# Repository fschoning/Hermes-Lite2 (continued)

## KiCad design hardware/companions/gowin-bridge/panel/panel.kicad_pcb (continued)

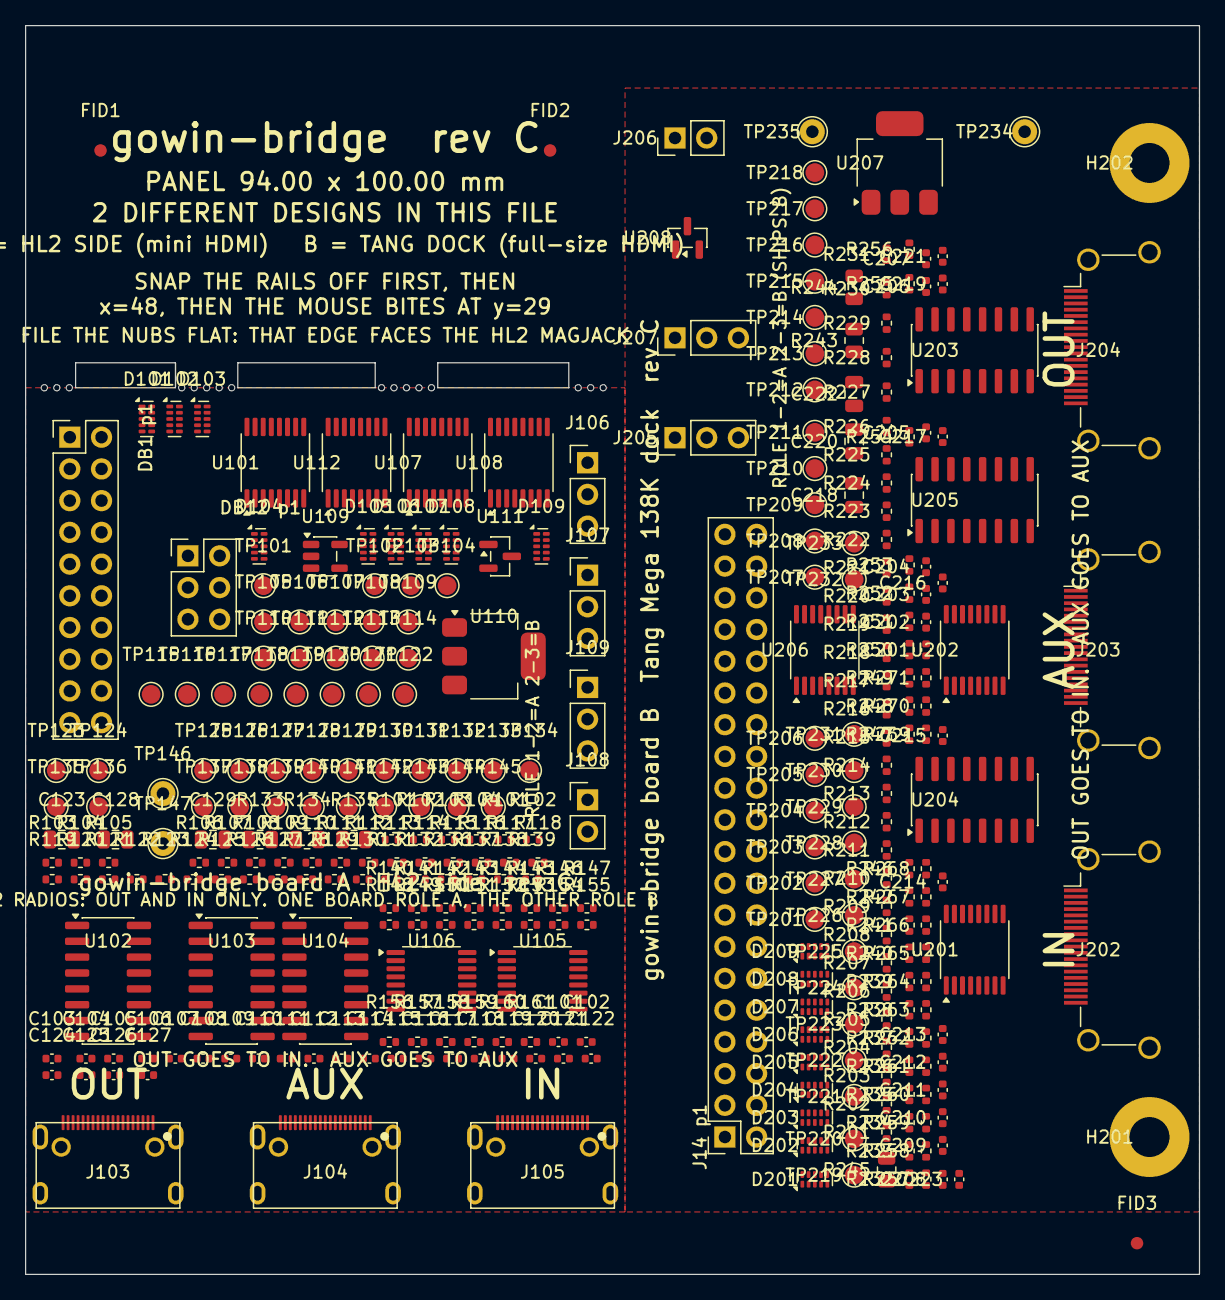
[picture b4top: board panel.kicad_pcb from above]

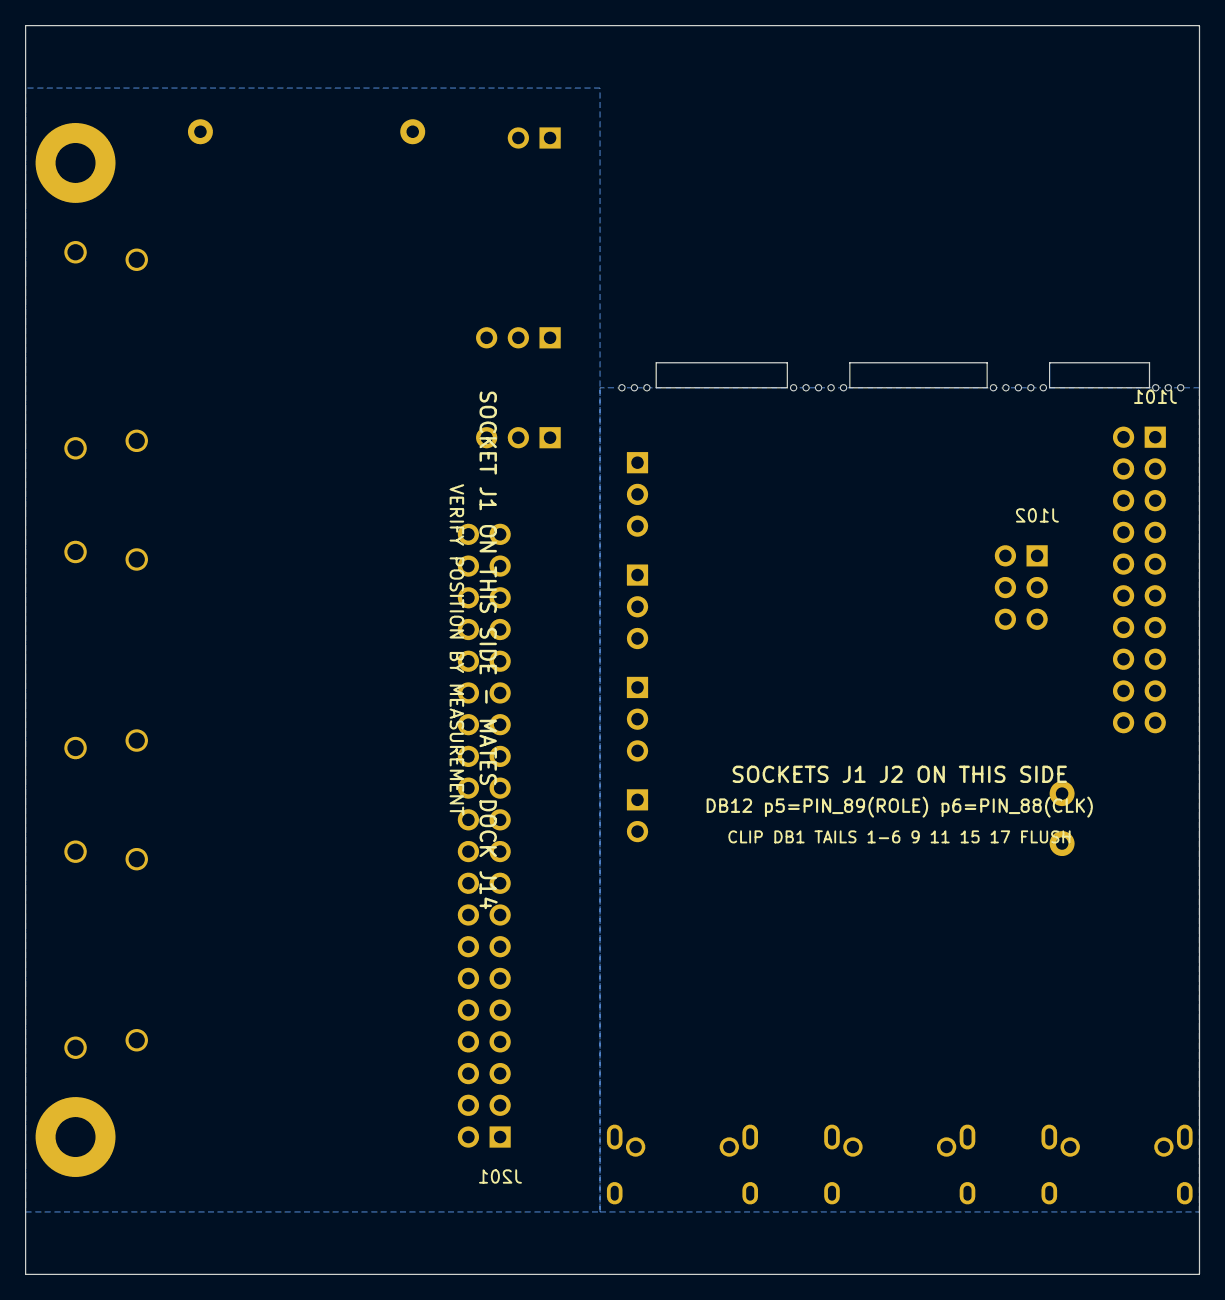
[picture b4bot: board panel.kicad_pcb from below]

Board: 4 copper layers, 94.0 x 100.0 mm, 345 parts (3 on the bottom side), 180 nets, no tracks yet.

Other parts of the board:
MB1, MB2, MB3, MB4, MB5, MB6, MB7, MB8, MB9, MB10, MB11, MB12, MB13, MB14, MB15, MB16: Drill
R101#2, R102#2, R103#2, R104#2: 10k; R_0402_1005Metric

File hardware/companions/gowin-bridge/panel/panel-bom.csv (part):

Designator,Value,Footprint,LCSC,MfrPart,Populate,Function,Note
C101,100nF,C_0402_1005Metric,C1525,,DNP,"AC-coupling option, I CLK P leg",NOT FITTED. Fit only together with the VBIAS network and remove the parallel 0 R link. Needs DC-balanced data; the gateware does not guarantee that.
C102,100nF,C_0402_1005Metric,C1525,,DNP,"AC-coupling option, I CLK N leg",NOT FITTED. Fit only together with the VBIAS network and remove the parallel 0 R link. Needs DC-balanced data; the gateware does not guarantee that.
C103,100nF,C_0402_1005Metric,C1525,,DNP,"AC-coupling option, I D0 P leg",NOT FITTED. Fit only together with the VBIAS network and remove the parallel 0 R link. Needs DC-balanced data; the gateware does not guarantee that.
C104,100nF,C_0402_1005Metric,C1525,,DNP,"AC-coupling option, I D0 N leg",NOT FITTED. Fit only together with the VBIAS network and remove the parallel 0 R link. Needs DC-balanced data; the gateware does not guarantee that.
C105,100nF,C_0402_1005Metric,C1525,,DNP,"AC-coupling option, I D1 P leg",NOT FITTED. Fit only together with the VBIAS network and remove the parallel 0 R link. Needs DC-balanced data; the gateware does not guarantee that.
C106,100nF,C_0402_1005Metric,C1525,,DNP,"AC-coupling option, I D1 N leg",NOT FITTED. Fit only together with the VBIAS network and remove the parallel 0 R link. Needs DC-balanced data; the gateware does not guarantee that.
C107,100nF,C_0402_1005Metric,C1525,,DNP,"AC-coupling option, I D2 P leg",NOT FITTED. Fit only together with the VBIAS network and remove the parallel 0 R link. Needs DC-balanced data; the gateware does not guarantee that.
C108,100nF,C_0402_1005Metric,C1525,,DNP,"AC-coupling option, I D2 N leg",NOT FITTED. Fit only together with the VBIAS network and remove the parallel 0 R link. Needs DC-balanced data; the gateware does not guarantee that.
C109,100nF,C_0402_1005Metric,C1525,,DNP,VBIAS bypass,NOT FITTED. Part of the AC-coupling option.
C110,100nF,C_0402_1005Metric,C1525,,yes,U1 VCCB,
C111,100nF,C_0402_1005Metric,C1525,,yes,U1 VCCA,
C112,100nF,C_0402_1005Metric,C1525,,yes,U12 VCCB,
C113,100nF,C_0402_1005Metric,C1525,,yes,U12 VCCA,
C114,100nF,C_0402_1005Metric,C1525,,yes,U2 VCC,
C115,100nF,C_0402_1005Metric,C1525,,yes,U3 VCC,
C116,100nF,C_0402_1005Metric,C1525,,yes,U4 VCC,
C117,100nF,C_0402_1005Metric,C1525,,yes,U5 VCC,
C118,100nF,C_0402_1005Metric,C1525,,yes,U6 VCC,
C119,100nF,C_0402_1005Metric,C1525,,yes,U7 VCCA,
C120,100nF,C_0402_1005Metric,C1525,,yes,U7 VCCB,
C121,100nF,C_0402_1005Metric,C1525,,yes,U8 VCCA,
C122,100nF,C_0402_1005Metric,C1525,,yes,U8 VCCB,
C123,10uF,C_0805_2012Metric,C15850,,yes,+3V3 bulk,
C124,100nF,C_0402_1005Metric,C1525,,yes,+3V3 bulk HF,
C125,1uF,C_0402_1005Metric,C52923,,yes,U9 output,
C126,100nF,C_0402_1005Metric,C1525,,yes,U9 input,
C127,100nF,C_0402_1005Metric,C1525,,yes,DB1 +3V3 entry,
C128,10uF,C_0805_2012Metric,C15850,,yes,U10 input bulk (option),
C129,10uF,C_0805_2012Metric,C15850,,yes,U10 output bulk (option),
C201,22pF,C_0402_1005Metric,C1555,,DNP,Optional ringing damper on LINK_SLOW_IN,NOT FITTED. 22 pF into 100 R is 2.2 ns. Fit if the unterminated cable wire rings enough to double-clock the receiver.
C202,100nF,C_0402_1005Metric,C1525,,DNP,"AC-coupling option, I CLK P leg",NOT FITTED. Fit only together with the VBIAS network and remove the parallel 0 R link. Needs DC-balanced data; the gateware does not guarantee that.
C203,100nF,C_0402_1005Metric,C1525,,DNP,"AC-coupling option, I CLK N leg",NOT FITTED. Fit only together with the VBIAS network and remove the parallel 0 R link. Needs DC-balanced data; the gateware does not guarantee that.
C204,100nF,C_0402_1005Metric,C1525,,DNP,"AC-coupling option, I D0 P leg",NOT FITTED. Fit only together with the VBIAS network and remove the parallel 0 R link. Needs DC-balanced data; the gateware does not guarantee that.
C205,100nF,C_0402_1005Metric,C1525,,DNP,"AC-coupling option, I D0 N leg",NOT FITTED. Fit only together with the VBIAS network and remove the parallel 0 R link. Needs DC-balanced data; the gateware does not guarantee that.
C206,100nF,C_0402_1005Metric,C1525,,DNP,"AC-coupling option, I D1 P leg",NOT FITTED. Fit only together with the VBIAS network and remove the parallel 0 R link. Needs DC-balanced data; the gateware does not guarantee that.
C207,100nF,C_0402_1005Metric,C1525,,DNP,"AC-coupling option, I D1 N leg",NOT FITTED. Fit only together with the VBIAS network and remove the parallel 0 R link. Needs DC-balanced data; the gateware does not guarantee that.
C208,100nF,C_0402_1005Metric,C1525,,DNP,"AC-coupling option, I D2 P leg",NOT FITTED. Fit only together with the VBIAS network and remove the parallel 0 R link. Needs DC-balanced data; the gateware does not guarantee that.
C209,100nF,C_0402_1005Metric,C1525,,DNP,"AC-coupling option, I D2 N leg",NOT FITTED. Fit only together with the VBIAS network and remove the parallel 0 R link. Needs DC-balanced data; the gateware does not guarantee that.
C210,100nF,C_0402_1005Metric,C1525,,DNP,VBIAS bypass,NOT FITTED. Part of the AC-coupling option.
C211,100nF,C_0402_1005Metric,C1525,,yes,U1 VCC,
C212,100nF,C_0402_1005Metric,C1525,,yes,U2 VCC,
C213,100nF,C_0402_1005Metric,C1525,,yes,U3 VCC,
C214,100nF,C_0402_1005Metric,C1525,,yes,U4 VCC,
C215,100nF,C_0402_1005Metric,C1525,,yes,U5 VCC,
C216,100nF,C_0402_1005Metric,C1525,,yes,U6 VCCA,
C217,100nF,C_0402_1005Metric,C1525,,yes,U6 VCCB,
C218,10uF,C_0805_2012Metric,C15850,,yes,+3V3 bulk,
C219,100nF,C_0402_1005Metric,C1525,,yes,+3V3 bulk HF,
C220,10uF,C_0805_2012Metric,C15850,,yes,5 V input bulk,
C221,100nF,C_0402_1005Metric,C1525,,yes,5 V input HF,
C222,10uF,C_0805_2012Metric,C15850,,yes,U7 output bulk,
C223,100nF,C_0402_1005Metric,C1525,,yes,extra +3V3,
D101,TPD4E05U06,USON-10_2.5x1.0mm_P0.5mm,C138714,TPD4E05U06DQAR,yes,"Quad 0.5 pF ESD array, 5.5 V, USON-10","Place within 5 mm of the HDMI connector pins, on the connector side of everything else."
D102,TPD4E05U06,USON-10_2.5x1.0mm_P0.5mm,C138714,TPD4E05U06DQAR,yes,"Quad 0.5 pF ESD array, 5.5 V, USON-10","Place within 5 mm of the HDMI connector pins, on the connector side of everything else."
D103,TPD4E05U06,USON-10_2.5x1.0mm_P0.5mm,C138714,TPD4E05U06DQAR,yes,"Quad 0.5 pF ESD array, 5.5 V, USON-10","Place within 5 mm of the HDMI connector pins, on the connector side of everything else."
D104,TPD4E05U06,USON-10_2.5x1.0mm_P0.5mm,C138714,TPD4E05U06DQAR,yes,"Quad 0.5 pF ESD array, 5.5 V, USON-10","Place within 5 mm of the HDMI connector pins, on the connector side of everything else."
D105,TPD4E05U06,USON-10_2.5x1.0mm_P0.5mm,C138714,TPD4E05U06DQAR,yes,"Quad 0.5 pF ESD array, 5.5 V, USON-10","Place within 5 mm of the HDMI connector pins, on the connector side of everything else."
D106,TPD4E05U06,USON-10_2.5x1.0mm_P0.5mm,C138714,TPD4E05U06DQAR,yes,"Quad 0.5 pF ESD array, 5.5 V, USON-10","Place within 5 mm of the HDMI connector pins, on the connector side of everything else."
D107,TPD4E05U06,USON-10_2.5x1.0mm_P0.5mm,C138714,TPD4E05U06DQAR,yes,"Quad 0.5 pF ESD array, 5.5 V, USON-10","Place within 5 mm of the HDMI connector pins, on the connector side of everything else."
D108,TPD4E05U06,USON-10_2.5x1.0mm_P0.5mm,C138714,TPD4E05U06DQAR,yes,"Quad 0.5 pF ESD array, 5.5 V, USON-10","Place within 5 mm of the HDMI connector pins, on the connector side of everything else."
D109,TPD4E05U06,USON-10_2.5x1.0mm_P0.5mm,C138714,TPD4E05U06DQAR,yes,"Quad 0.5 pF ESD array, 5.5 V, USON-10","Place within 5 mm of the HDMI connector pins, on the connector side of everything else."
D201,TPD4E05U06,USON-10_2.5x1.0mm_P0.5mm,C138714,TPD4E05U06DQAR,yes,"Quad 0.5 pF ESD array, 5.5 V, USON-10","Place within 5 mm of the HDMI connector pins, on the connector side of everything else."
D202,TPD4E05U06,USON-10_2.5x1.0mm_P0.5mm,C138714,TPD4E05U06DQAR,yes,"Quad 0.5 pF ESD array, 5.5 V, USON-10","Place within 5 mm of the HDMI connector pins, on the connector side of everything else."
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
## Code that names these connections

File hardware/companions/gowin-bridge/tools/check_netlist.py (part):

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    5:  ('HL2_ADC_D2', '83', 'ADC sample data 2 out'),
    6:  ('HL2_AUX_CLK_OUT', '85', 'auxiliary clock out'),
    7:  ('VLVDS', '-', 'HL2 2.5 V rail, tap only, unused by default'),
    8:  ('VLVDS', '-', 'same net as pin 7'),
    9:  ('HL2_FWD_CLK_RAW', '98', 'forward clock 153.6 MHz out, before the '
                                  'divider. Carries LED D2 through R71'),
    10: ('HL2_CWR', '90', 'CW/PTT ring - AUXIO line 0, NOT an LED pin'),
    11: ('HL2_TX_D0', '99', 'transmit data 0 in. Carries LED D3 through R72'),
    12: ('HL2_CWT', '91', 'CW/PTT tip - AUXIO line 1, NOT an LED pin'),
    13: ('GND', '-', 'ground'),
    14: ('GND', '-', 'ground'),
    15: ('HL2_TX_D1', '100', 'transmit data 1 in. Carries LED D4 through R73'),
    16: ('HL2_SCL1', '103', 'I2C1 SCL - AUXIO line 2, NOT an LED pin'),
    17: ('HL2_TX_D2', '101', 'transmit data 2 in. Carries LED D5 through R74'),
    18: ('HL2_SDA1', '104', 'I2C1 SDA - AUXIO line 3, NOT an LED pin'),
    19: ('DB1_3V3', '-', 'board supply, before FB1'),
    20: ('DB1_3V3', '-', 'same net as pin 19'),
}
# NOTE pins 5 and 6.  DB12 pin 5 is FPGA PIN_89 and pin 6 is PIN_88, per
# hardware/hl/hermeslite.net.  rev A of PINMAP.md had these two swapped and
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            prob.append('%s should reach %s through one %s, found %s'
                        % (cnet, hnet, val, rs))
    pd = [r for (r, _) in bynet.get('G_TCK_DRV', []) if r.startswith('R')
          and {pins.get((r, '1')), pins.get((r, '2'))} == {'G_TCK_DRV',
                                                            'G_GND'}]
    if not pd:
        prob.append('G_TCK_DRV has no pull-down, so an unconfigured Gowin '
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        prob.append('%s OE* is %s, not the presence-interlocked AUXIO_OE_N'
                    % (AUXIO_DRIVE_BUF, sorted(oe)))
        return prob
    ups, downs = pulls('AUXIO_OE_N', pins, vals, bynet, byref)
    q = [r for (r, pd) in bynet.get('AUXIO_OE_N', [])
         if r.startswith('Q') and pd == '3']
    other = [r for (r, _) in bynet.get('AUXIO_OE_N', [])
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    # link-alive gate (a second MOSFET whose gate is LINK_ALIVE)
    q2 = [r for (r, pd) in bynet.get(src, []) if r.startswith('Q')
          and pd == '3']
    via_la = (len(q2) == 1 and pins.get((q2[0], '1')) == 'LINK_ALIVE'
              and pins.get((q2[0], '2')) == 'AUXIO_EN_N')
    if gate != 'SB_PRSNT_IN' or not via_la or gu or not gd:
        prob.append('the interlock %s must have gate SB_PRSNT_IN (pulled '
                    'DOWN, so LOW with the far end absent) and its source must '
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}
# The scenario model's inputs: what the radio FPGA can do to the enables and
# the forward clock, and what the far end does to presence.
RADIO_CLOCK_NET = 'HL2_FWD_CLK'          # after the pin 98 divider
GATEWARE_ENABLE_NETS = {'HL2_JTAG_EN': 'pin80', 'HL2_AUXIO_EN': 'pin72'}
PRESENCE_NET = 'SB_PRSNT_IN'             # J1 contact B8
DETECTOR_OUT = 'LINK_ALIVE'
HL2_HEADERS = ('J2', 'J3', 'J4')
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    # the radio end as the near end: its gated parts
    gated = []
    for r in ('U4', 'U5'):
        if 'SB_PRSNT_IN' in resolve_links(n, n.pins.get((r, '1'))):
            gated.append(r)
    if any(n.fitted(r) and n.vals.get(r) == '0R' and {
            n.pins.get((r, '1')), n.pins.get((r, '2'))} == {'DRV_EN', '+3V3'}
            for r in n.byref):
        prob.append('a FITTED 0 R ties DRV_EN to +3V3: the LVDS drivers run '
                    'with no far end')
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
